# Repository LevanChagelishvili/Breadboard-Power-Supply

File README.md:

# Breadboard-Power-Supply
Breadboard Power Supply for Arduino and electronics

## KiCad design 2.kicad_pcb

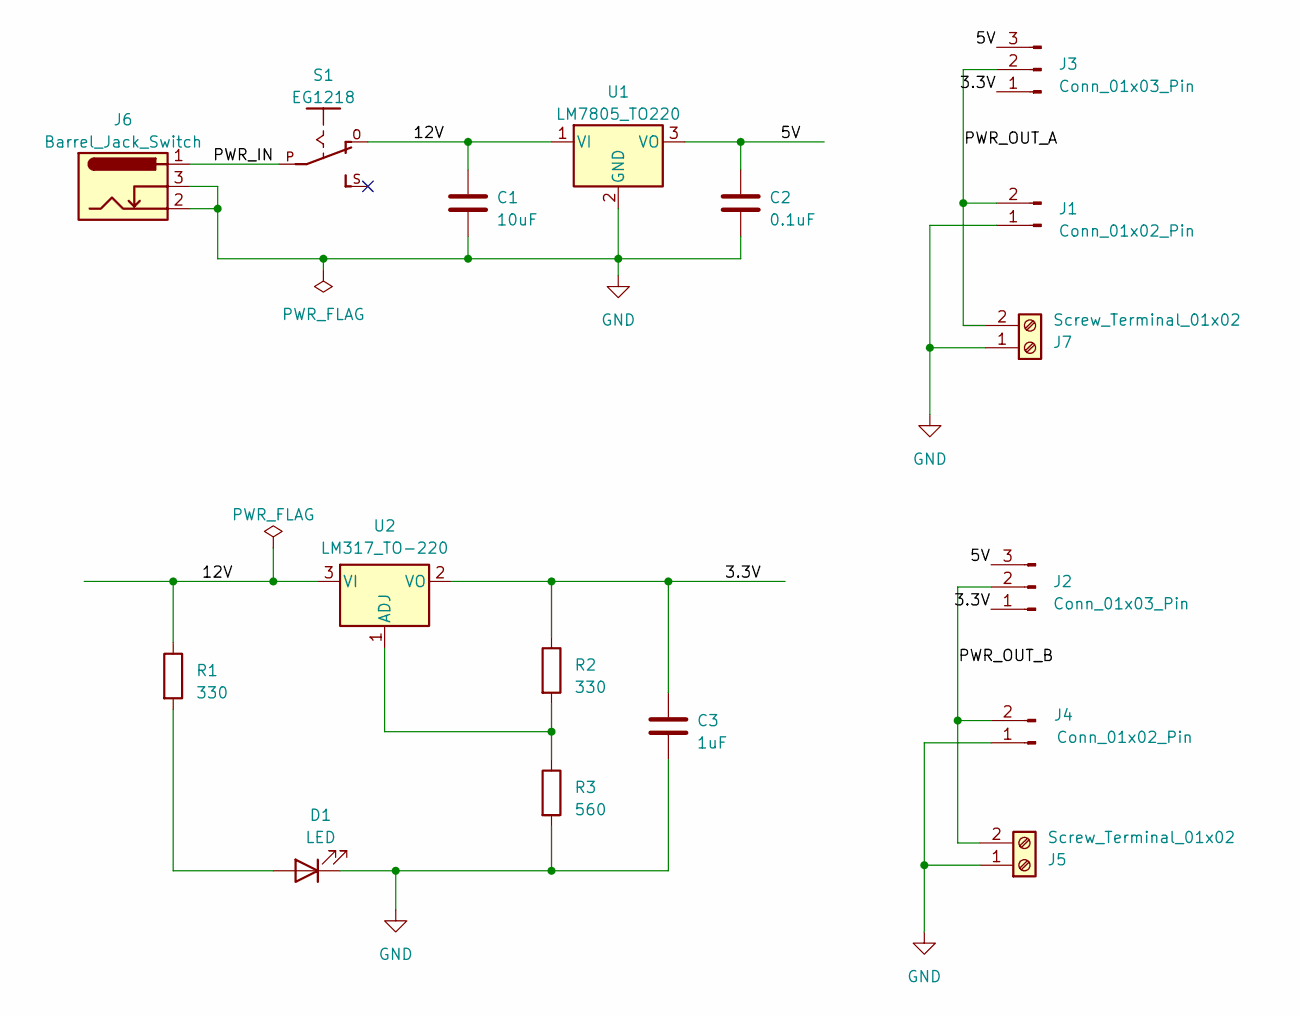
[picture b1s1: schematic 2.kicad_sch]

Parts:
C1: 10uF; C_Disc_D3.0mm_W1.6mm_P2.50mm
C2: 0.1uF; C_Disc_D3.0mm_W1.6mm_P2.50mm
C3: 1uF; C_Disc_D3.0mm_W1.6mm_P2.50mm
D1: LED; LED_D5.0mm
J1, J4: Conn_01x02_Pin; PinHeader_1x02_P2.54mm_Vertical
J2, J3: Conn_01x03_Pin; PinHeader_1x03_P2.54mm_Vertical
J5, J7: Screw_Terminal_01x02; TerminalBlock_bornier-2_P5.08mm
J6: Barrel_Jack_Switch; BarrelJack_Horizontal
R1, R2: 330; R_Axial_DIN0204_L3.6mm_D1.6mm_P7.62mm_Horizontal
R3: 560; R_Axial_DIN0204_L3.6mm_D1.6mm_P7.62mm_Horizontal
S1: EG1218
U1: LM7805_TO220; TO-220-3_Vertical
U2: LM317_TO-220; TO-220-3_Vertical

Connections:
/3.3V: C3.1, J2.1, J3.1, R2.1, U2.2 (VO)
/5V: C2.1, J2.3, J3.3, U1.3 (VO)
/12V: C1.1, R1.1, S1.O, U1.1 (VI), U2.3 (VI)
/PWR_IN: J6.1, S1.P
/PWR_OUT_A: J1.2, J3.2, J7.2
/PWR_OUT_B: J2.2, J4.2, J5.2
GND: C1.2, C2.2, C3.2, D1.1 (K), J1.1, J4.1, J5.1, J6.2, J6.3, J7.1, R3.2, U1.2 (GND)
unnamed: D1.2 (A), R1.2
unnamed: R2.2, R3.1, U2.1 (ADJ)

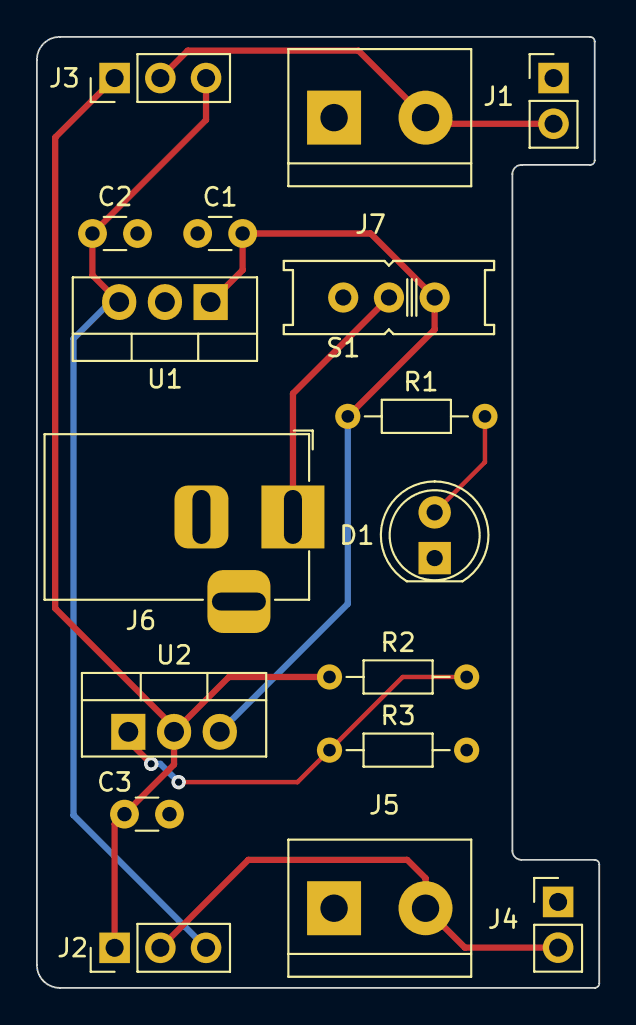
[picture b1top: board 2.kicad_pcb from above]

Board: 2 copper layers, 31.2 x 52.8 mm, 17 parts (0 on the bottom side), 9 nets.
